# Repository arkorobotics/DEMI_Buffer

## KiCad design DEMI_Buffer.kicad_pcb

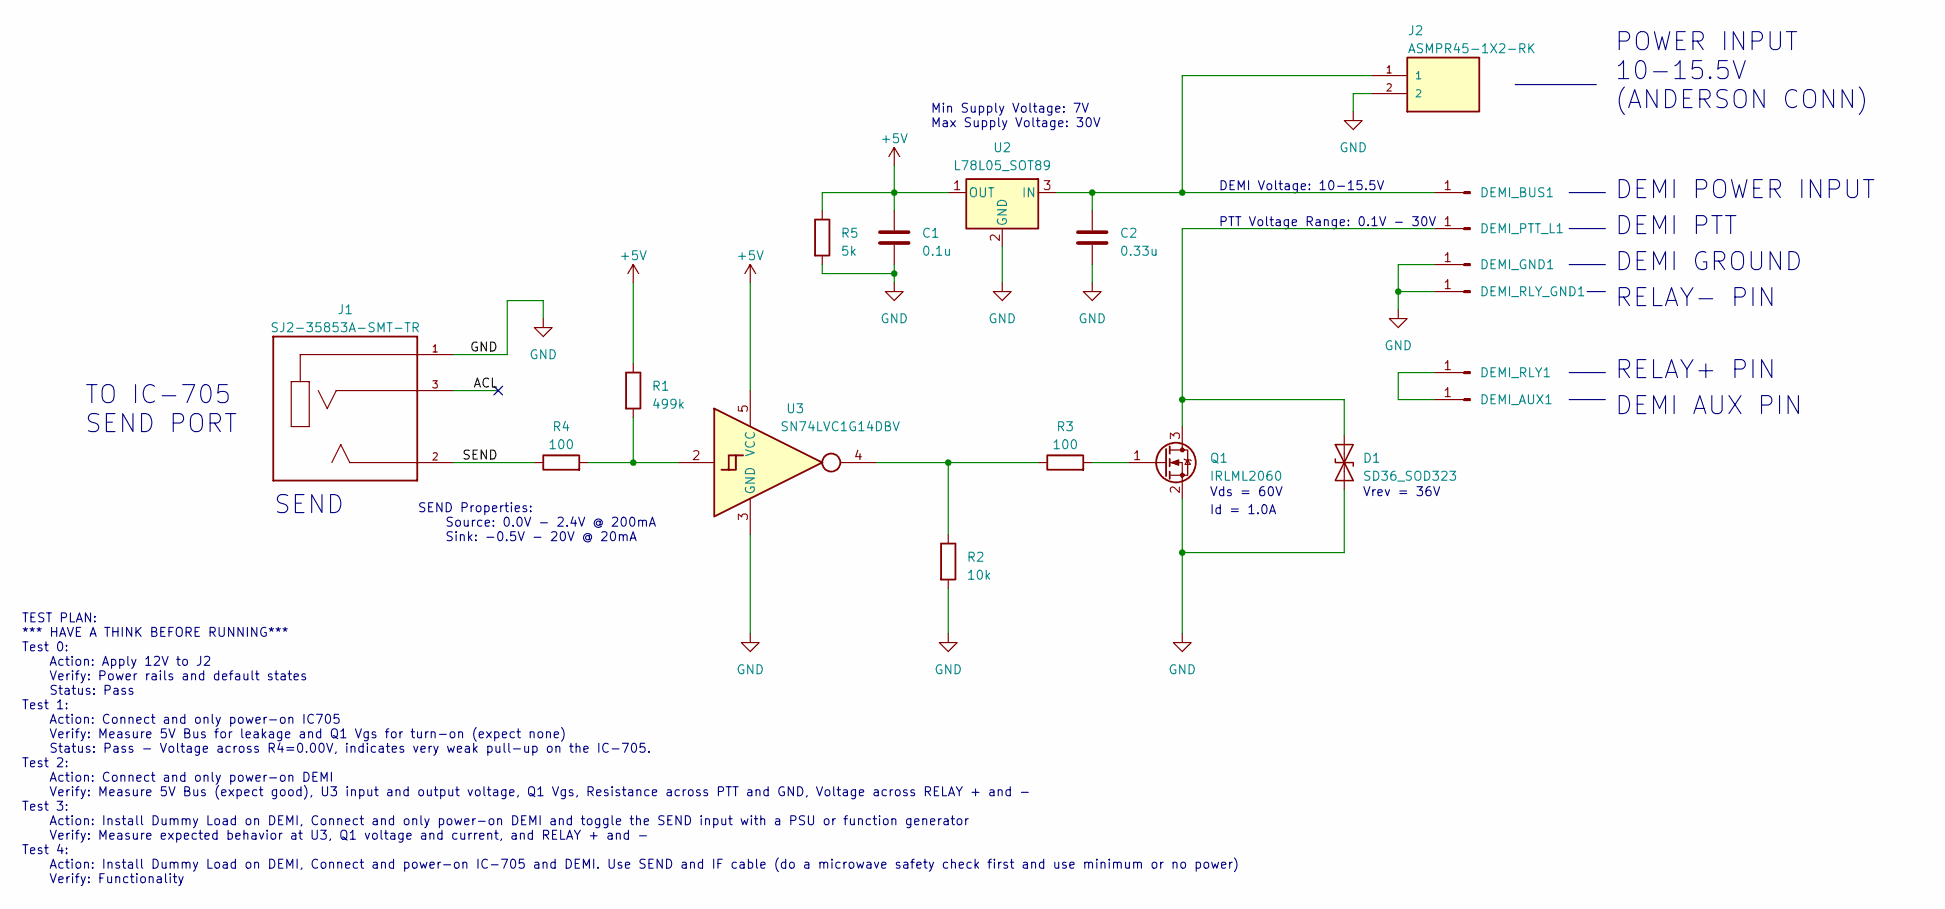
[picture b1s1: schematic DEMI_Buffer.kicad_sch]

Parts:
C1: 0.1u; C_0603_1608Metric
C2: 0.33u; C_0603_1608Metric
D1: SD36_SOD323; D_SOD-323
DEMI_AUX1: Conn_01x01_Pin; SolderWirePad_1x01_SMD_2.5x5mm
DEMI_BUS1: Conn_01x01_Pin; SolderWirePad_1x01_SMD_3x6mm
DEMI_GND1: Conn_01x01_Pin; SolderWirePad_1x01_SMD_3x6mm
DEMI_PTT_L1: Conn_01x01_Pin; SolderWirePad_1x01_SMD_2.5x5mm
DEMI_RLY1: Conn_01x01_Pin; SolderWirePad_1x01_SMD_2.5x5mm
DEMI_RLY_GND1: Conn_01x01_Pin; SolderWirePad_1x01_SMD_2.5x5mm
J1: SJ2-35853A-SMT-TR; CUI_SJ2-35853A-SMT-TR; MPN SJ2-35853A-SMT-TR
J2: ASMPR45-1X2-RK; APP_ASMPR45-1X2-RK; PARTREV N/A
Q1: IRLML2060; SOT-23
R1: 499k; R_0603_1608Metric
R2: 10k; R_0603_1608Metric
R3, R4: 100; R_0603_1608Metric
R5: 5k; R_0603_1608Metric
U2: L78L05_SOT89; SOT-89-3
U3: SN74LVC1G14DBV; SOT-23-5

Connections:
+5V: C1.1, R1.1, R5.1, U2.1 (OUT), U3.5 (VCC)
/ACL: J1.3
/SEND: J1.2, R4.1
GND: C1.2, C2.2, D1.1 (A1), DEMI_GND1.1, DEMI_RLY_GND1.1, J1.1, J2.2, Q1.2 (S), R2.2, R5.2, U2.2 (GND), U3.3 (GND)
unnamed: D1.2 (A2), DEMI_PTT_L1.1, Q1.3 (D)
unnamed: DEMI_AUX1.1, DEMI_RLY1.1
unnamed: C2.1, DEMI_BUS1.1, J2.1, U2.3 (IN)
unnamed: Q1.1 (G), R3.2
unnamed: R1.2, R4.2, U3.2
unnamed: R2.1, R3.1, U3.4

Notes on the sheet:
PTT Voltage Range: 0.1V - 30V
DEMI PTT
DEMI GROUND
RELAY- PIN
DEMI AUX PIN
SEND
TO IC-705 SEND PORT
RELAY+ PIN
TEST PLAN: *** HAVE A THINK BEFORE RUNNING*** Test 0: Action: Apply 12V to J2 Verify: Power rails and default states Status: Pass Test 1: Action: Connect and only power-on IC705 Verify: Measure 5V Bus for leakage and Q1 Vgs for turn-on (expect none) Status: Pass - Voltage across R4=0.00V, indicates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
DEMI Voltage: 10-15.5V
Id = 1.0A
DEMI POWER INPUT
POWER INPUT 10-15.5V (ANDERSON CONN)
SEND Properties: Source: 0.0V - 2.4V @ 200mA Sink: -0.5V - 20V @ 20mA
Vrev = 36V
Min Supply Voltage: 7V Max Supply Voltage: 30V
Vds = 60V

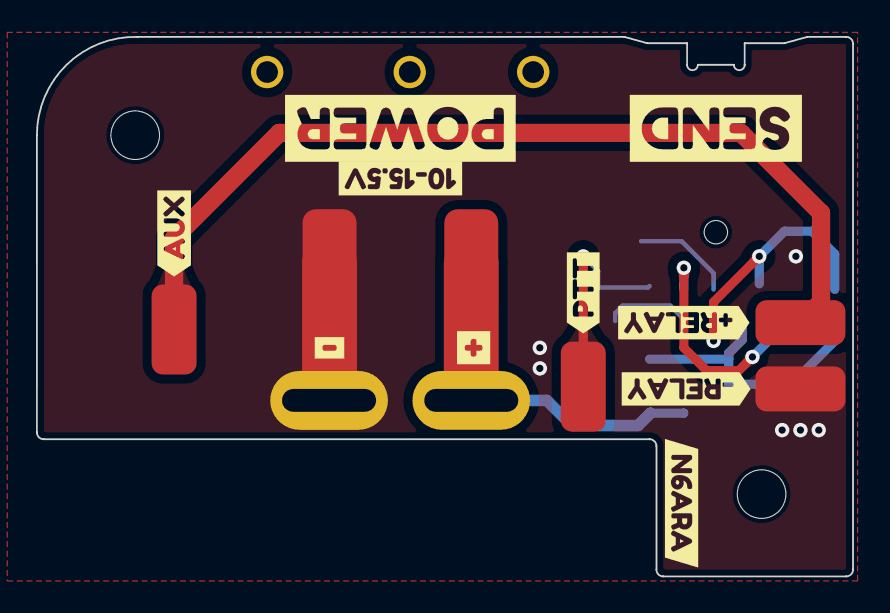
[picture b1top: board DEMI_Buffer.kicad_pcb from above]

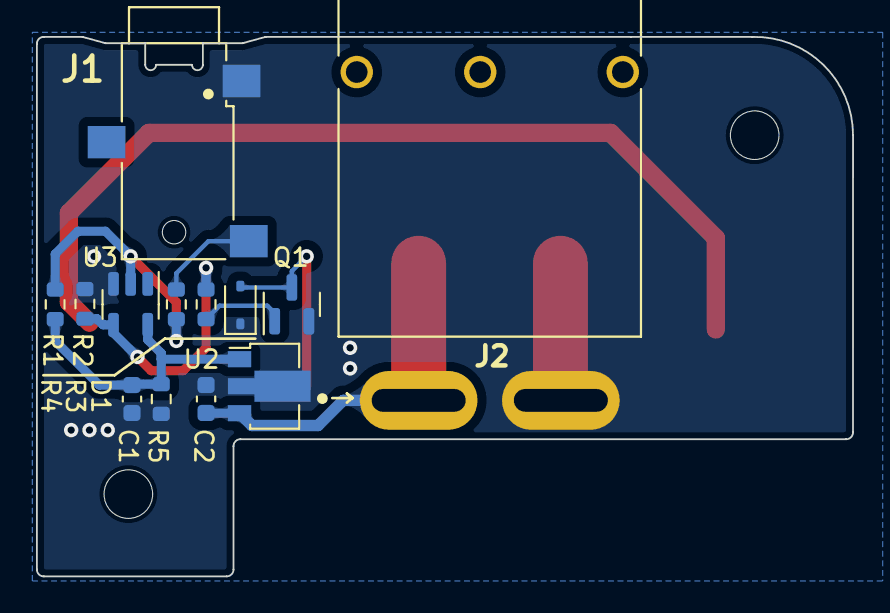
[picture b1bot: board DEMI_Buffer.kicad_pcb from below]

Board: 2 copper layers, 45.3 x 30.0 mm, 29 parts (13 on the bottom side), 9 nets.

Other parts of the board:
kibuzzard-63FD1EDA: G***; kibuzzard-63FD1EDA
kibuzzard-63FD1EF5: G***; kibuzzard-63FD1EF5
kibuzzard-63FD36AA: G***; kibuzzard-63FD36AA
kibuzzard-63FD37BB: G***; kibuzzard-63FD37BB
kibuzzard-63FD37D3: G***; kibuzzard-63FD37D3
kibuzzard-63FD203D: G***; kibuzzard-63FD203D
kibuzzard-63FD370C: G***; kibuzzard-63FD370C
kibuzzard-63FD371C: G***; kibuzzard-63FD371C
kibuzzard-63FD3696: G***; kibuzzard-63FD3696
kibuzzard-63FD7275: G***; kibuzzard-63FD7275

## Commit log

2023-05-14 Initial Commit
    Initial Commit
2023-05-27 Cleaned up the repo a bit
    Cleaned up the repo a bit
